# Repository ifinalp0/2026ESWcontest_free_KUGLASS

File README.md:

# KUGLASS

KUGLASS는 카메라와 내부온도에 따라 1:10 차량 모형의 PDLC를 CH0~CH3으로
능동 제어하는 시연용 프로토타입입니다. ESP32_A가 센서와 제어 정책을 담당하고,
ESP32_B가 제작된 Logic Carrier와 단일 채널 Power Stage PCB 4장을 통해 실제
출력을 담당합니다.

> 이 저장소는 모형 시연용 개발 자산입니다. 실차 안전 장치나 자율주행 인지
> 성능 향상 장치를 표방하지 않습니다.

## 시스템 구성

```mermaid
flowchart LR
    CAM[카메라] --> A[ESP32_A<br/>입력·정책·목표 MI]
    TEMP[DS18B20 내부온도] --> A
    A -->|UART JSON Lines<br/>20 Hz + TTL| B[ESP32_B<br/>검증·4채널 SPWM·safe-off]
    B --> LC[Logic Carrier<br/>E-Stop gate·Fault·ADC]
    LC --> PS[Power Stage ×4]
    PS --> PDLC[PDLC CH0~CH3]
    B -->|적용 MI·Fault·ADC| A
    UI[브라우저] <-->|HTTP| TAB[MacBook TabUI]
    TAB <-->|micro-USB<br/>USB Serial/JTAG CDC| A
```

- 입력: 카메라 1대, YwRobot SEN050007 DS18B20 내부온도센서 모듈 1개
- 출력: PDLC CH0 운전석 창문, CH1 조수석 창문·선루프, CH2 운전석 옆 창문,
  CH3 조수석 옆 창문
- MI 의미: 값이 클수록 CLEAR이며 현재 운용 상한 0.60이 완전 투명 방향입니다.
  0.0 또는 disable은 safe-off·강산란 방향입니다.
- 제어 우선순위: `E-Stop > latched Fault > Manual(관리자 지속/일반 TTL) > Demo/Auto`

ESP32_A가 권위 있는 목표 MI를 계산합니다. ESP32_B는 목표를 다시 계산하지 않고
명령 검증, 출력, 로컬 차단과 실제 적용 상태 회신만 수행합니다. TabUI는 LIVE
자동 정책을 계산하지 않습니다.

ESP32_A와 ESP32_B는 Logic Carrier를 통하지 않는 외부 3선 UART harness로
연결합니다.

```text
ESP32_A GPIO39 TX -> ESP32_B GPIO44 RX
ESP32_A GPIO40 RX <- ESP32_B GPIO43 TX
ESP32_A GND       --- ESP32_B GND
```

UART1은 115200 8-N-1이며 TX↔RX를 교차 연결합니다. TX끼리 또는 RX끼리 연결하지
않습니다.

더 자세한 책임과 물리 연결은 [시스템 구조](docs/ARCHITECTURE.md), frame 형식은
[통신 계약](docs/PROTOCOL.md)을 참고하세요.

## 저장소 구조

| 경로 | 역할 | 시작 문서 |
| --- | --- | --- |
| `TabUI/` | MacBook 백엔드, 브라우저 HMI, ESP32_A USB gateway | [TabUI README](TabUI/README.md) |
| `ESP32_A_Algo/` | 카메라·온도, 정책, 목표 MI, A→B 통신 제품 펌웨어 | [ESP32_A README](ESP32_A_Algo/README.md) |
| `ESP32_B_Algo/` | 4채널 SPWM, 채널별 Fault와 전역 TTL safe-off 제품 펌웨어 | [ESP32_B README](ESP32_B_Algo/README.md) |
| `hardware/` | as-built 회로 원본, 기계 판독 계약, HIL 절차 | [hardware README](hardware/README.md) |
| `docs/` | 시스템 구조, 통신, 검증 공통 문서 | [문서 안내](docs/README.md) |
| `For_Test/` | 사용자가 대상을 지정할 때만 보는 독립 시험 코드 | [시험 영역 안내](For_Test/README.md) |
| `Simul_Twin/` | production과 분리된 디지털 트윈, 수정 금지 | [Simul_Twin README](Simul_Twin/README.md) |
| `Ioniq 3D model/` | UI에 사용하는 차량 3D 원본과 라이선스 | [모델 라이선스](Ioniq%203D%20model/hyundai_ioniq_5_-_lowpoly/license.txt) |

제품에 빌드·플래시하는 canonical firmware는 `ESP32_A_Algo/`와
`ESP32_B_Algo/`뿐입니다. 각 폴더의 `host_tests/`는 제품 계약의 일부이며,
`For_Test/`의 독립 시험 firmware와 구분합니다.

## 문서 안내

| 문서 | 독자와 용도 |
| --- | --- |
| [README.md](README.md) | 처음 보는 개발자를 위한 개요와 실행 진입점 |
| [AGENTS.md](AGENTS.md) | AI 에이전트의 작업 범위, 금지사항과 검증 규칙 |
| [개발 계획서.md](개발%20계획서.md) | 작품의 배경, 목표와 개발 계획 |
| [docs/ARCHITECTURE.md](docs/ARCHITECTURE.md) | 컴포넌트 책임, 데이터 흐름과 runtime mode |
| [docs/PROTOCOL.md](docs/PROTOCOL.md) | TabUI↔A↔B wire contract와 reset 절차 |
| [docs/VALIDATION.md](docs/VALIDATION.md) | 변경 범위별 자동 검사와 HIL 요약 |
| [hardware/README.md](hardware/README.md) | 제작 하드웨어의 기준 자료와 읽는 순서 |

AI를 사용할 때는 루트 [AGENTS.md](AGENTS.md)를 단일 진입점으로 사용합니다.

## 빠른 시작: TabUI

Node.js 22+와 Python 3.11+를 권장합니다.

```bash
cd TabUI
npm ci
npm run setup:python
npm run check
npm run build
npm start
```

ESP32_A DevKit의 USB 단자를 데이터 micro-USB 케이블로 MacBook에 연결한 뒤
`http://localhost:8080/demo`을 엽니다. 기본 LIVE 설정은 `transport=usb`,
`usb-port=auto`이며 macOS의 단일 `/dev/cu.usbmodem*` 장치를 자동 탐색합니다.

ESP32_A 없이 UI만 실행하려면 MOCK을 명시합니다.

```bash
cd TabUI
.venv/bin/python server.py --transport mock
```

현재 서버는 인증 없는 plain HTTP 시연 구성입니다. localhost 또는 신뢰된 격리
LAN에서만 사용하세요. 자세한 USB 선택, 개발 서버와 API는
[TabUI README](TabUI/README.md)에 있습니다.

## 펌웨어 빌드

두 제품 firmware는 ESP-IDF 6.0.2와 ESP32-S3를 기준으로 합니다.

```bash
cd ESP32_A_Algo
idf.py set-target esp32s3
idf.py build
```

```bash
cd ESP32_B_Algo
idf.py set-target esp32s3
idf.py build
```

플래시, 핀과 HIL 조건은 각 firmware README를 먼저 확인하세요. ESP32_B와 전력부
작업은 반드시 [하드웨어 기준](hardware/README.md)의 읽기 순서와 안전 조건을
따라야 합니다.

## 현재 구현과 미확정 범위

현재 저장소에는 다음 항목이 구현되어 있습니다.

- ESP32_A 카메라·DS18B20 입력, 정책, 관리자 지속/일반 TTL 수동 제어, 20 Hz A→B heartbeat
- ESP32_B strict full-frame 검증, 4채널 16 kHz/60 Hz SPWM, 채널별 Fault 차단과
  timeout 전체 safe-off
- boot/session/challenge에 묶인 Fault reset과 결과 correlation
- ESP32_B ADC 8채널 raw/mV 및 validity telemetry와 TabUI의 TH1 데이터시트 기반
  채널별 명목 온도 표시
- TabUI LIVE/MOCK/REPLAY 상태 분리, 명령 gateway와 on-demand 카메라 영상
- TabUI 독립 관리자 콘솔의 A/B 통신·센서·ADC 진단과 채널별 지속 Enable/MI 제어
- 제작 완료된 Logic Carrier 1장과 동일 단일 채널 Power Stage PCB 4장의 원본·계약

다음 항목은 저장소에 실측 완료 기록이 없으므로 확정값으로 사용하지 않습니다.

- 보드별 전류 A·온도 °C calibration과 protection threshold
- GPIO/connector 연속성, 부팅·reset 파형, Fault trip latency
- MI-Vrms-투과도 LUT와 카메라 개선 수치
- Power Stage 열·절연·고전압 통합 성능

상세 상태는
[`hardware/validation/current-status.json`](hardware/validation/current-status.json)을
참고하세요.

## 검증

```bash
python3 hardware/tools/validate_hardware_contract.py

cd TabUI
npm run check
npm run build

cd ../ESP32_A_Algo
sh host_tests/run_tests.sh

cd ../ESP32_B_Algo
sh host_tests/run_tests.sh

cd ..
sh hardware/validation/BAD_JSON/host_tests/run_tests.sh
```

하드웨어 validator와 host test 통과는 Power Stage/PDLC/HV 실기 검증을 대신하지
않습니다. 변경별 검사 범위와 HIL 항목은 [검증 가이드](docs/VALIDATION.md)를
참고하세요.

## 핵심 안전 주의

- ESP32_B는 제작된 Logic Carrier U3에 장착하고, Power Stage에 임의 직결하지 않습니다.
- J5 E-Stop은 enable만 차단합니다. +24/+12/+5/+72 V rail은 계속 live일 수 있습니다.
- ADC raw/mV를 calibration 전 전류 A나 보정 완료 온도처럼 표시하지 않습니다.
  TabUI의 `T °C (명목)`은 유효한 mV에 TH1 데이터시트 모델을 적용한 진단값이며
  보호 판단에는 사용하지 않습니다.
- 실제 Power Stage와 고전압은 logic-only·저전압 검증을 먼저 통과한 뒤 연결합니다.
- 상세 실기 절차는 [하드웨어 검증 문서](hardware/validation/README.md)를 따릅니다.

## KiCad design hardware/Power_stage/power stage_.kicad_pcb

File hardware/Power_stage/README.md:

# Power Stage as-built 기준

이 폴더는 현재 제작된 단일 채널 Power Stage의 기준 자료입니다. 동일한 보드 네 장을 Logic Carrier J7의 CH0~CH3에 한 장씩 연결합니다. 회로와 PCB 내부의 `CH0`은 단일 보드 내부 이름이며 시스템 채널은 연결된 J7 블록이 결정합니다.

## 원본의 역할

| 파일 | 역할 |
| --- | --- |
| `power stage_.kicad_sch` | editable as-built schematic |
| `power stage_.kicad_pcb` | editable as-built PCB layout |
| `power stage_.kicad_pro` | KiCad project 설정 |
| `power stage_.kicad_dru` | 저장된 custom design rule |
| `Power_stage.pdf` | 1페이지 schematic release view |
| `datasheets/` | U1/U2, U5, U13, U14와 TH1 부품 자료 |

`datasheets/TH1.pdf`는 2024년 9월판 TDK NTCG series catalog입니다. 회로의
TH1 조건인 10 kΩ@25 °C와 `2012Metric/EIA 0805` footprint에 동시에 맞는 catalog
항목은 `NTCG203NH103JT1`입니다. 이는 제공된 자료에 따른 설계상 catalog match이며,
조립 BOM 또는 실물 확인을 대신하지 않습니다.

회로 연결과 명목 계산값의 기계 판독 기준은 [`../contracts/power_stage.json`](../contracts/power_stage.json)입니다.

## 회로 구성

- J8: `+72V_HV` DC bus 입력
- Q1-Q4: H-Bridge MOSFET
- U1/U2: IRS2104 half-bridge driver, +12 V 공급
- U13: 74LVC04 direction inversion
- U14: 74LVC08 PWM routing과 `RUN_OK`
- L1/L2 470 uH와 C10 470 nF: differential output filter
- J9: filtered `PDLC_A/PDLC_B` 출력
- R9 0.1 ohm: PGND와 logic GND 사이 current shunt
- U5 TLV1701: open-collector `FAULT_N_CH0`
- R14 10 kohm과 TH1 10 kohm NTC: temperature feedback divider

논리식은 다음과 같습니다.

```text
DIR_N_CH0    = NOT DIR_CH0
PWM_LEFT_CH0 = PWM_MAG_CH0 AND DIR_CH0
PWM_RIGHT_CH0 = PWM_MAG_CH0 AND DIR_N_CH0
RUN_OK_CH0   = CH0_ENABLE AND FAULT_N_CH0
```

`RUN_OK_CH0`가 두 IRS2104의 active-low shutdown을 구동합니다. Power Stage의 fault LOW는 펌웨어 polling과 별개로 양쪽 driver를 shutdown합니다.

## J10 인터페이스

| 홀수 핀 | 신호 | 짝수 핀 |
| ---: | --- | --- |
| 1 | `PWM_MAG_CH0` | 2 GND |
| 3 | `DIR_CH0` | 4 GND |
| 5 | `CH0_ENABLE` | 6 GND |
| 7 | `FAULT_N_CH0` | 8 GND |
| 9 | `ADC_I_CH0_RAW` | 10 GND |
| 11 | `ADC_TEMP_CH0_RAW` | 12 GND |
| 13 | +3.3 V | 14 GND |
| 15 | +12 V | 16 GND |

J10 홀수 핀의 상대 위치는 Logic Carrier J7 각 채널 block의 홀수 핀과 같습니다.

## 명목 feedback 값과 사용 범위

- Current: R9 0.1 ohm이므로 이상적인 DC shunt 값은 0.1 V/A입니다. R10 10 kohm/C8 100 nF를 거쳐 raw ADC로 전달됩니다.
- Comparator: R12 33 kohm/R13 1 kohm의 명목 기준은 약 97.1 mV이고, R9 값으로 나눈 명목 trip은 약 0.971 A입니다.
- Temperature: R14 10 kohm과 TH1 10 kohm@25 °C의 명목 분압은 25 °C에서 약 1.65 V입니다.
  `NTCG203NH103JT1`의 catalog 값은 B25/50=3590 K, B25/75=3635 K,
  B25/85=3650 K, B25/100=3670 K, R25 허용오차 ±5%, B 허용오차 ±3%,
  동작 범위 -40~125 °C입니다.

ESP32_B firmware는 계속 raw/mV만 회신합니다. TabUI는 유효한 mV telemetry에만
다음 B25/85 단일-beta 명목 모델을 적용해 `T °C (명목)`을 표시합니다.

```text
V = t_mv / 1000
R_NTC = 10000 * V / (3.3 - V)
T_C = 1 / (1 / 298.15 + ln(R_NTC / 10000) / 3650) - 273.15
```

`t_raw`는 ESP32-S3 ADC의 비선형성과 칩별 calibration 때문에
`raw * 3300 / 4095`로 변환하지 않습니다. ESP32_B가 12 dB attenuation에서
`adc_cali_raw_to_voltage()` curve-fitting으로 만든 유효 `t_mv`를 먼저 사용합니다.
0 mV나 3300 mV 이상, mV invalid, 또는 위 모델 결과가 catalog 동작 범위 밖이면
TabUI는 °C를 표시하지 않습니다.

3.3 V 명목 조건에서 TH1의 divider 자기발열 전력은 R_NTC=R14=10 kΩ일 때 최대
약 0.272 mW입니다. catalog의 2012 size 방열계수 2 mW/°C를 그대로 적용하면
catalog 시험 환경에서의 명목 자기발열은 약 0.136 °C입니다. 실제 보드에서는
3.3 V rail, R14 허용오차, 장착 부품, 열결합, ADC 오차와 보드별 편차가 남으므로
TabUI 값은 실측 calibration이나 protection 기준이 아닙니다. 정확한 nominal R-T
table과 보드별 보정이 확보되면 단일-beta 모델의 잔차를 다시 검증해야 합니다.

## 현재 자료의 충돌과 경계

- Q1-Q4 schematic value는 `STP40NF20`이지만 각 Datasheet 속성은 IRF540N URL입니다. 실제 장착 marking 확인 전에는 MOSFET 정격을 어느 쪽으로도 단정하지 않습니다.
- PCB 파일은 2-layer, 1.6 mm, layer당 0.035 mm copper로 설정되어 있습니다. schematic note의 `2 oz copper preferred`는 실제 제작 copper weight 기록이 아닙니다.
- schematic에는 72 V/switching node 주변 1.5 mm clearance 지침이 있습니다. 이를 인증된 절연 등급으로 해석하지 않습니다.
- custom symbol/footprint library table이 없어 KiCad ERC에서 library resolution warning이 발생합니다. symbol과 footprint 데이터는 현재 schematic/PCB에 embed되어 있습니다.
- `kicad-cli pcb drc`는 현재 저장된 PCB/DRU 조합에서 정상 보고서 대신 tool crash로 종료됩니다. DRC 통과로 표시하지 않습니다.
- Gerber, drill, placement, 조립 BOM, 네 보드의 serial/revision 대응표는 저장소에 없습니다.

물리적으로 제작된 보드라는 사실과 EDA 자동 검사 상태는 별개입니다. 소프트웨어 작업에서는 이 회로를 현재 하드웨어로 존중하고, 확인되지 않은 제조값이나 실측값을 추가로 가정하지 않습니다.

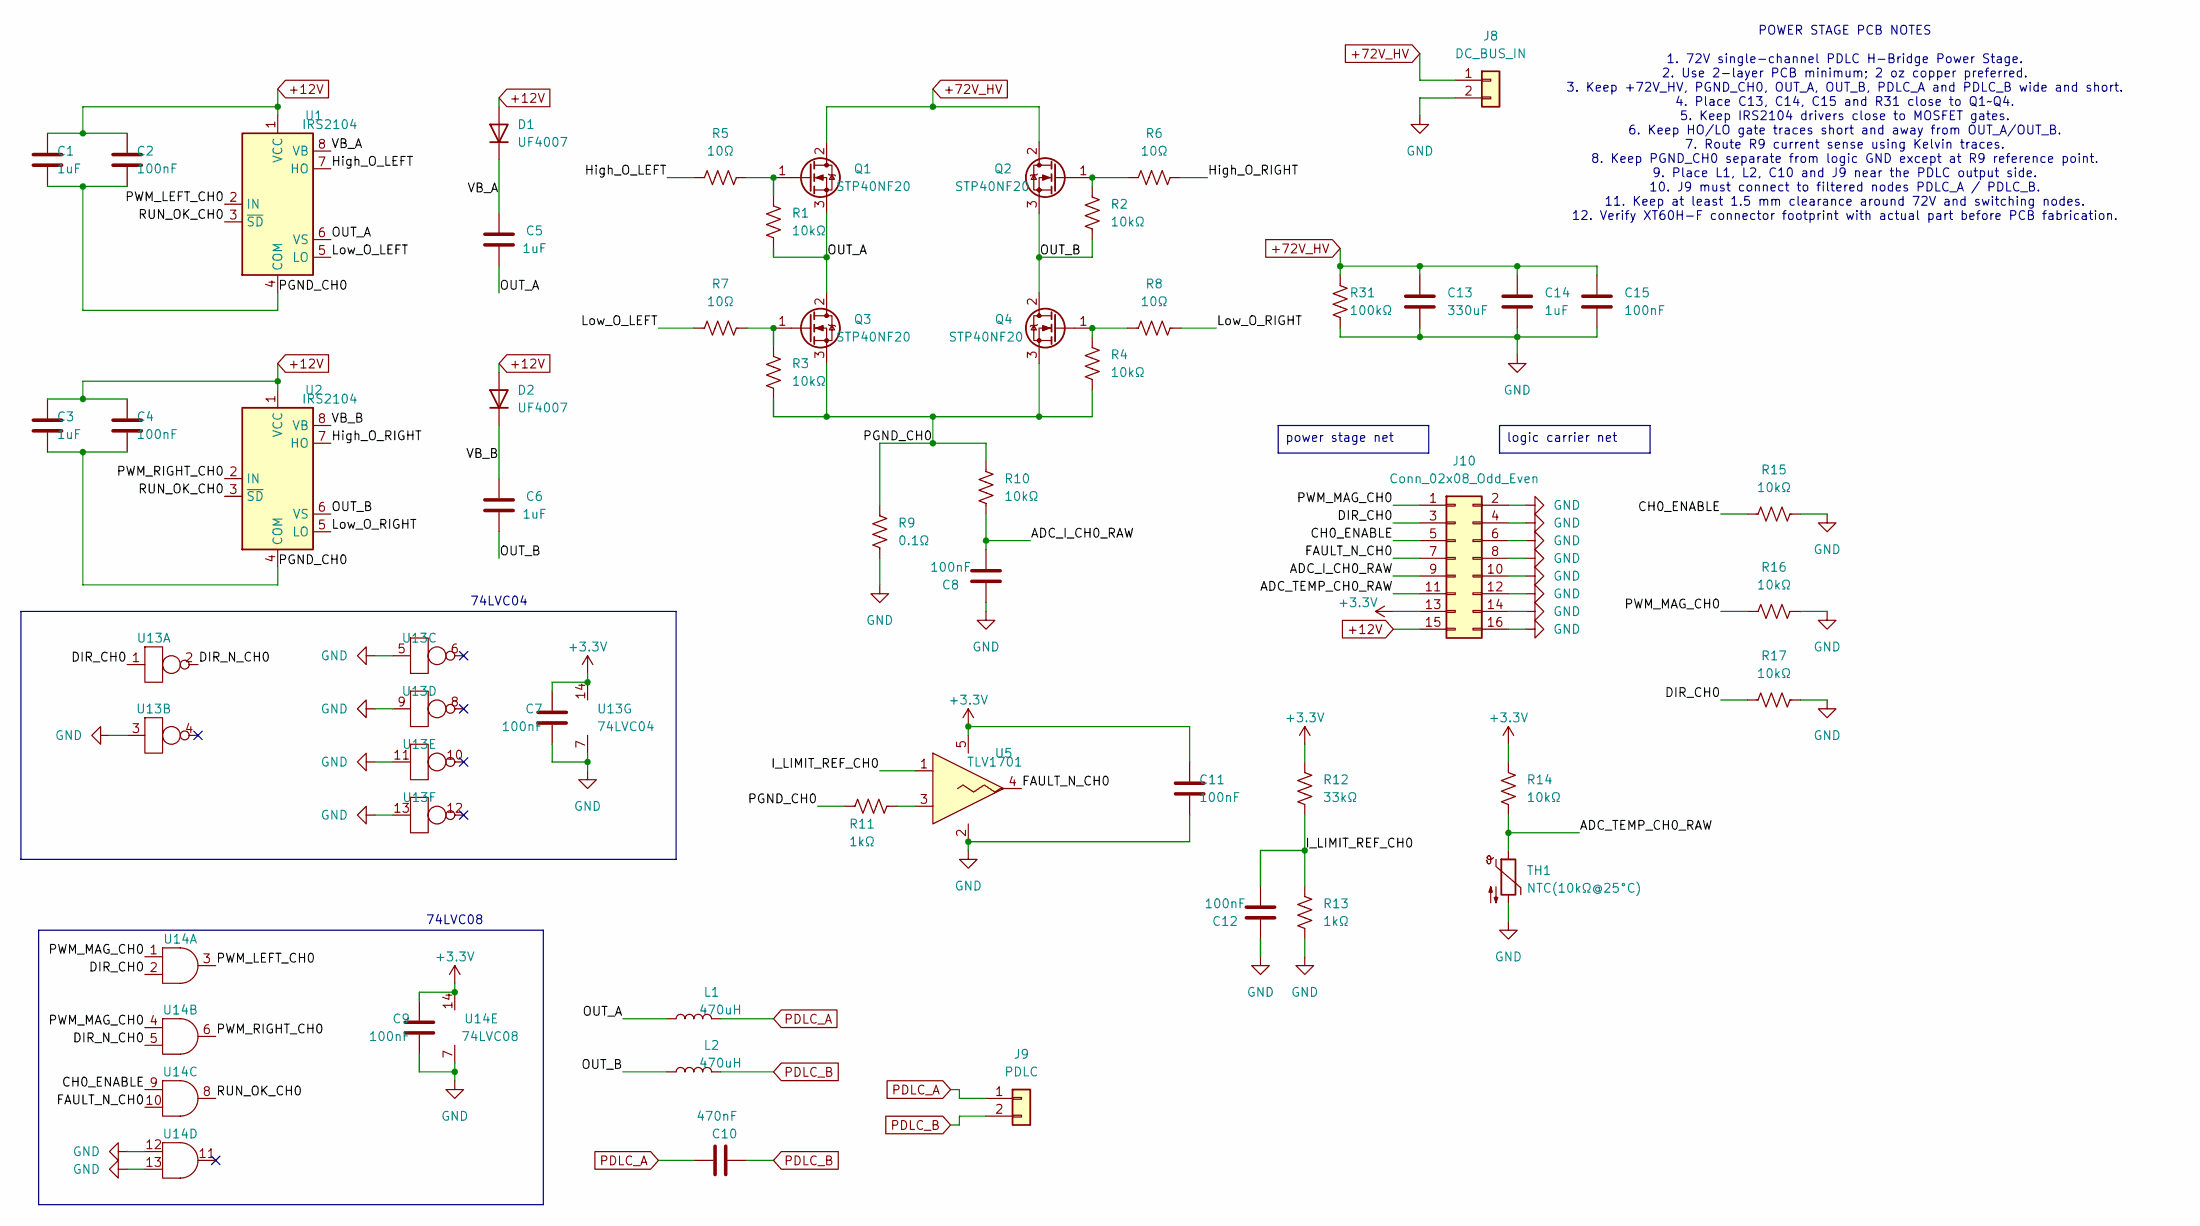
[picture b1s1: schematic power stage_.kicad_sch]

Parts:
C1, C3, C5, C6: 1uF; C_1206_3216Metric
C2, C4, C7, C8, C9, C11, C12, C15: 100nF; C_1206_3216Metric
C10: 470nF; C_1210_3225Metric
C13: 330uF; CP_Radial_D18.0mm_P7.50mm
C14: 1uF; C_1812_4532Metric
D1, D2: UF4007; D_DO-41_SOD81_P10.16mm_Horizontal
J8: DC_BUS_IN; XT60H-F_CLEARANCE_1p6mm
J9: PDLC; XT60H-F_CLEARANCE_1p6mm
J10: Conn_02x08_Odd_Even; IDC-Header_2x08_P2.54mm_Vertical
L1, L2: 470uH; L_Radial_D18.0mm_P10.00mm
Q1, Q2, Q3, Q4: STP40NF20; TO-220-3_Vertical
R1, R2, R3, R4, R10, R14, R15, R16, R17: 10kΩ; R_0603_1608Metric
R5, R6, R7, R8: 10Ω; R_0805_2012Metric
R9: 0.1Ω; R_2512_6332Metric
R11, R13: 1kΩ; R_0603_1608Metric
R12: 33kΩ; R_0603_1608Metric
R31: 100kΩ; R_2010_5025Metric
TH1: NTC(10kΩ@25°C); R_0805_2012Metric
U1, U2: IRS2104; SOIC-8_3.9x4.9mm_P1.27mm
U5: TLV1701; SOT-23-5
U13: 74LVC04; TSSOP-14_4.4x5mm_P0.65mm
U14: 74LVC08; TSSOP-14_4.4x5mm_P0.65mm

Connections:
+3.3V: C7.1, C9.1, C11.1, J10.13, R12.1, R14.1, U5.5 (V+), U13.14 (VCC), U14.14 (VCC)
+12V: C1.1, C2.1, C3.1, C4.1, D1.2 (A), D2.2 (A), J10.15, U1.1 (VCC), U2.1 (VCC)
+72V_HV: C13.1, C14.1, C15.1, J8.1, Q1.2 (D), Q2.2 (D), R31.1; also elsewhere on the board
/ADC_I_CH0_RAW: C8.1, J10.9, R10.2
/ADC_TEMP_CH0_RAW: J10.11, R14.2, TH1.1
/CH0_ENABLE: J10.5, R15.1, U14.9 (A)
/DIR_CH0: J10.3, R17.1, U13.1 (A), U14.2 (B)
/DIR_N_CH0: U13.2 (Y), U14.5 (B)
/FAULT_N_CH0: J10.7, U5.4 (OUT), U14.10 (B)
/High_O_LEFT: R5.1, U1.7 (HO)
/High_O_RIGHT: R6.2, U2.7 (HO)
/I_LIMIT_REF_CH0: C12.1, R12.2, R13.1, U5.1 (IN+)
/Low_O_LEFT: R7.1, U1.5 (LO)
/Low_O_RIGHT: R8.2, U2.5 (LO)
/OUT_A: C5.1, L1.1, Q1.3 (S), Q3.2 (D), R1.1, U1.6 (VS); also elsewhere on the board
/OUT_B: C6.1, L2.1, Q2.3 (S), Q4.2 (D), R2.1, U2.6 (VS)
/PGND_CH0: C1.2, C2.2, C3.2, C4.2, Q3.3 (S), Q4.3 (S), R3.1, R4.1, R9.1, R10.1, R11.1, U1.4 (COM), U2.4 (COM); also elsewhere on the board
/PWM_LEFT_CH0: U1.2 (IN), U14.3 (Y)
/PWM_MAG_CH0: J10.1, R16.1, U14.1 (A), U14.4 (A)
/PWM_RIGHT_CH0: U2.2 (IN), U14.6 (Y)
/RUN_OK_CH0: U1.3 (~SD), U2.3 (~SD), U14.8 (Y)
/VB_A: C5.2, D1.1 (K), U1.8 (VB)
/VB_B: C6.2, D2.1 (K), U2.8 (VB)
GND: C7.2, C8.2, C9.2, C11.2, C12.2, C13.2, C14.2, C15.2, J8.2, J10.2, J10.4, J10.6, J10.8, J10.10, J10.12, J10.14, J10.16, R9.2, R13.2, R15.2, R16.2, R17.2, R31.2, TH1.2, U5.2 (V-), U13.3 (A), U13.5 (A), U13.7 (GND), U13.9 (A), U13.11 (A), U13.13 (A), U14.7 (GND), U14.12 (A), U14.13 (B); also elsewhere on the board
unnamed: Q1.1 (G), R1.2, R5.2
unnamed: Q2.1 (G), R2.2, R6.1
unnamed: Q3.1 (G), R3.2, R7.2
unnamed: Q4.1 (G), R4.2, R8.1
unnamed: R11.2, U5.3 (IN-)
PDLC_A: C10.2, J9.1, L1.2
PDLC_B: C10.1, J9.2, L2.2

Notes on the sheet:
74LVC04
74LVC08
POWER STAGE PCB NOTES 1. 72V single-channel PDLC H-Bridge Power Stage. 2. Use 2-layer PCB minimum; 2 oz copper preferred. 3. Keep +72V_HV, PGND_CH0, OUT_A, OUT_B, PDLC_A and PDLC_B wide and short. 4. Place C13, C14, C15 and R31 close to Q1~Q4. 5. Keep IRS2104 drivers close to MOSFET gates. 6. Keep 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
power stage net
logic carrier net

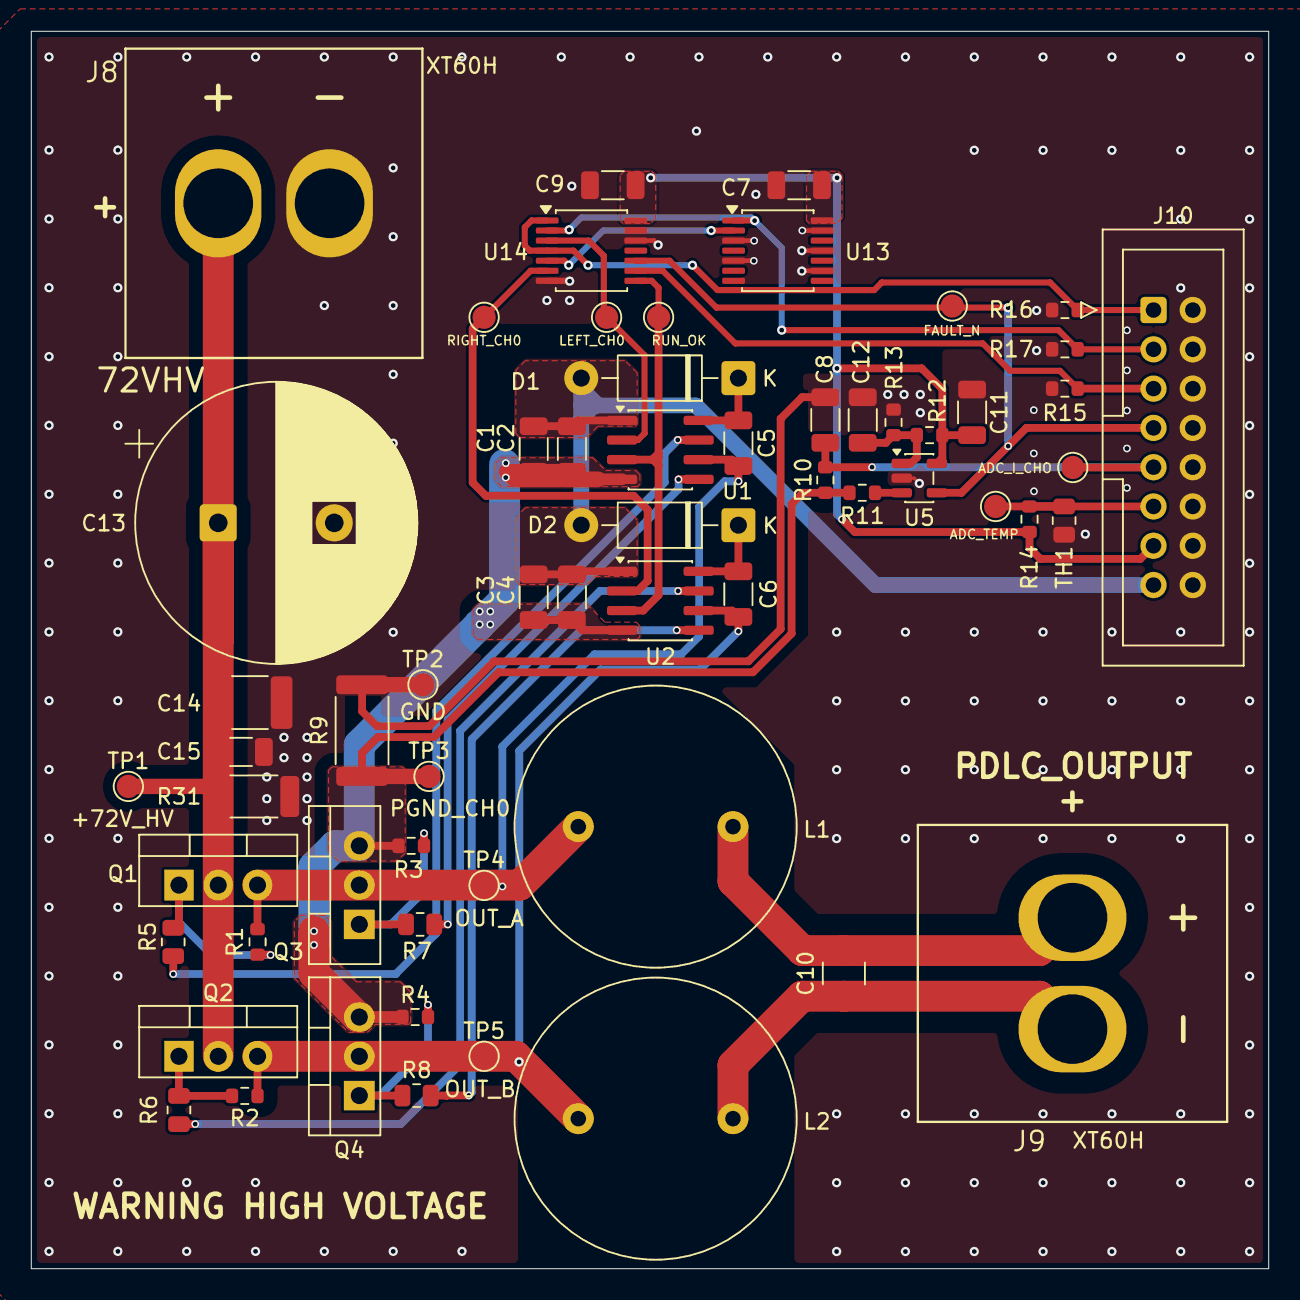
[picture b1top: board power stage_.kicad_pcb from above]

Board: 2 copper layers, 80.0 x 80.0 mm, 61 parts (0 on the bottom side), 31 nets.

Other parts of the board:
ADC_I_CHO: ADC_I; TestPoint_THTPad_D1.5mm_Drill0.7mm
ADC_TEMP: ADC_TEMP; TestPoint_THTPad_D1.5mm_Drill0.7mm
FAULT_N: LEFT_CH0; TestPoint_THTPad_D1.5mm_Drill0.7mm
LEFT_CH0: LEFT_CH0; TestPoint_THTPad_D1.5mm_Drill0.7mm
RIGHT_CH0: RIGHT_CH0; TestPoint_THTPad_D1.5mm_Drill0.7mm
RUN_OK: RUN_OK; TestPoint_THTPad_D1.5mm_Drill0.7mm
TP1: +72V_HV; TestPoint_THTPad_D1.5mm_Drill0.7mm
TP2: GND; TestPoint_THTPad_D1.5mm_Drill0.7mm
TP3: PGND_CH0; TestPoint_THTPad_D1.5mm_Drill0.7mm
TP4: OUT_A; TestPoint_THTPad_D1.5mm_Drill0.7mm
TP5: OUT_B; TestPoint_THTPad_D1.5mm_Drill0.7mm

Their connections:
+72V_HV: TP1.1; also elsewhere on the board
/OUT_A: TP4.1; also elsewhere on the board
/PGND_CH0: TP3.1; also elsewhere on the board
GND: TP2.1; also elsewhere on the board
